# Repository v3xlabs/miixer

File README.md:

# MIIXER

An open-hardware midi controller with esp32-c3, 4 linear faders, 8 keyswitches.

> [!NOTE]
> This is a work in progress.

## Technical Specs

- **Processor**: esp32-s3
- **Inputs**
  - 4 linear potentiometers 600mm
  - 8 Cherry MX Switches
- **ICs**
  - [PCF8574T](https://jlcpcb.com/api/file/downloadByFileSystemAccessId/8624297452529963008) - I2C IO Expander
  - [ADS1115IDGS](https://jlcpcb.com/api/file/downloadByFileSystemAccessId/8624297452529963008) - I2C ADC Expander
  - [AP2127K-3.3](https://www.diodes.com/assets/Datasheets/AP2127.pdf) - 5v to 3.3v LDO
  - [USBLC6-2SC6](https://www.st.com/resource/en/datasheet/usblc6-2.pdf) - ESD Protection
- **Connectivity**:
  - USB-C (Power, Data & Flash)
  - Wifi & BLE

## Photos

See the [docs](docs) folder for the rendered schematics, PCBs, and 3D renders.

## ESPHome Compatability

Due to the fact that this devices uses common off-the-shelf I2C ICs and is esp32-c3 based, you can easily use it with ESPHome.

```yaml
# TODO: This yaml file is work in progress, its ment to give an impression, its has not been confirmed functional.
i2c:
  sda: GPIO8
  scl: GPIO9
  scan: true

# 4x Fader Input
ads1115:
  address: 0x48 # todo confirm
  update_interval: 5s
  # todo interrupt pin (io6)

# 4x Fader LEDs
tcl59208f:
  id: led_drv # optional
  address: # todo

# 8x Keyswitch Input
pcf8574:
  id: expander # optional
  address: 0x20 # todo confirm
  # todo interrupt pin (io7)

binary_sensor:
  # 8x Keyswitch Input
  - platform: pcf8574
    pin: P0
    name: "Switch 1"
    # todo add 7 more pins

sensor:
  # 4x Fader Analog Input
  - platform: ads1115
    multiplexer: 'A0_GND' # todo
    gain: 6.144 # todo
    # todo 3 more pins

output:
  # 4x Fader LEDs
  - platform: tcl59208f
    driver: led_drv # optional
    id: led1
    channel: 0
  - platform: tcl59208f
    driver: led_drv # optional
    id: led2
    channel: 1
  - platform: tcl59208f
    driver: led_drv # optional
    id: led3
    channel: 2
  - platform: tcl59208f
    driver: led_drv # optional
    id: led4
    channel: 3

light:
  # 4x Fader SK6812
  - platform: fastled_clockless
    chipset: SK6812
    pin: GPIO3
    num_leds: 4
    rgb_order: GRB
    name: "SK6812 Array"
```

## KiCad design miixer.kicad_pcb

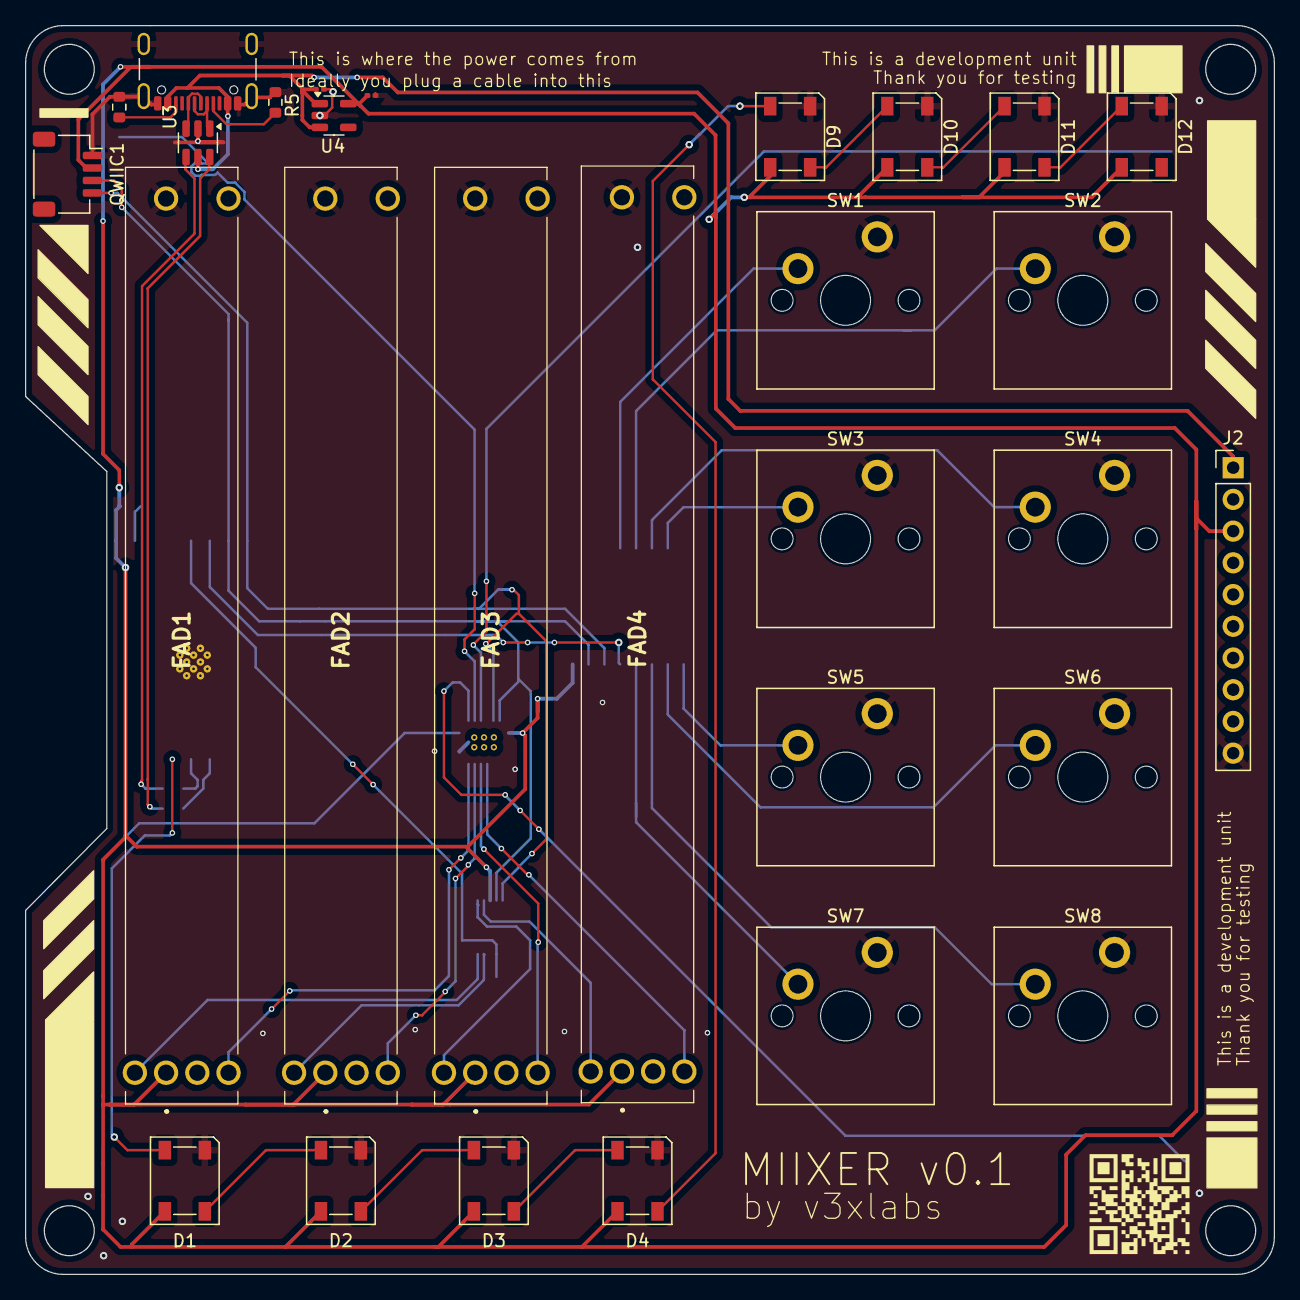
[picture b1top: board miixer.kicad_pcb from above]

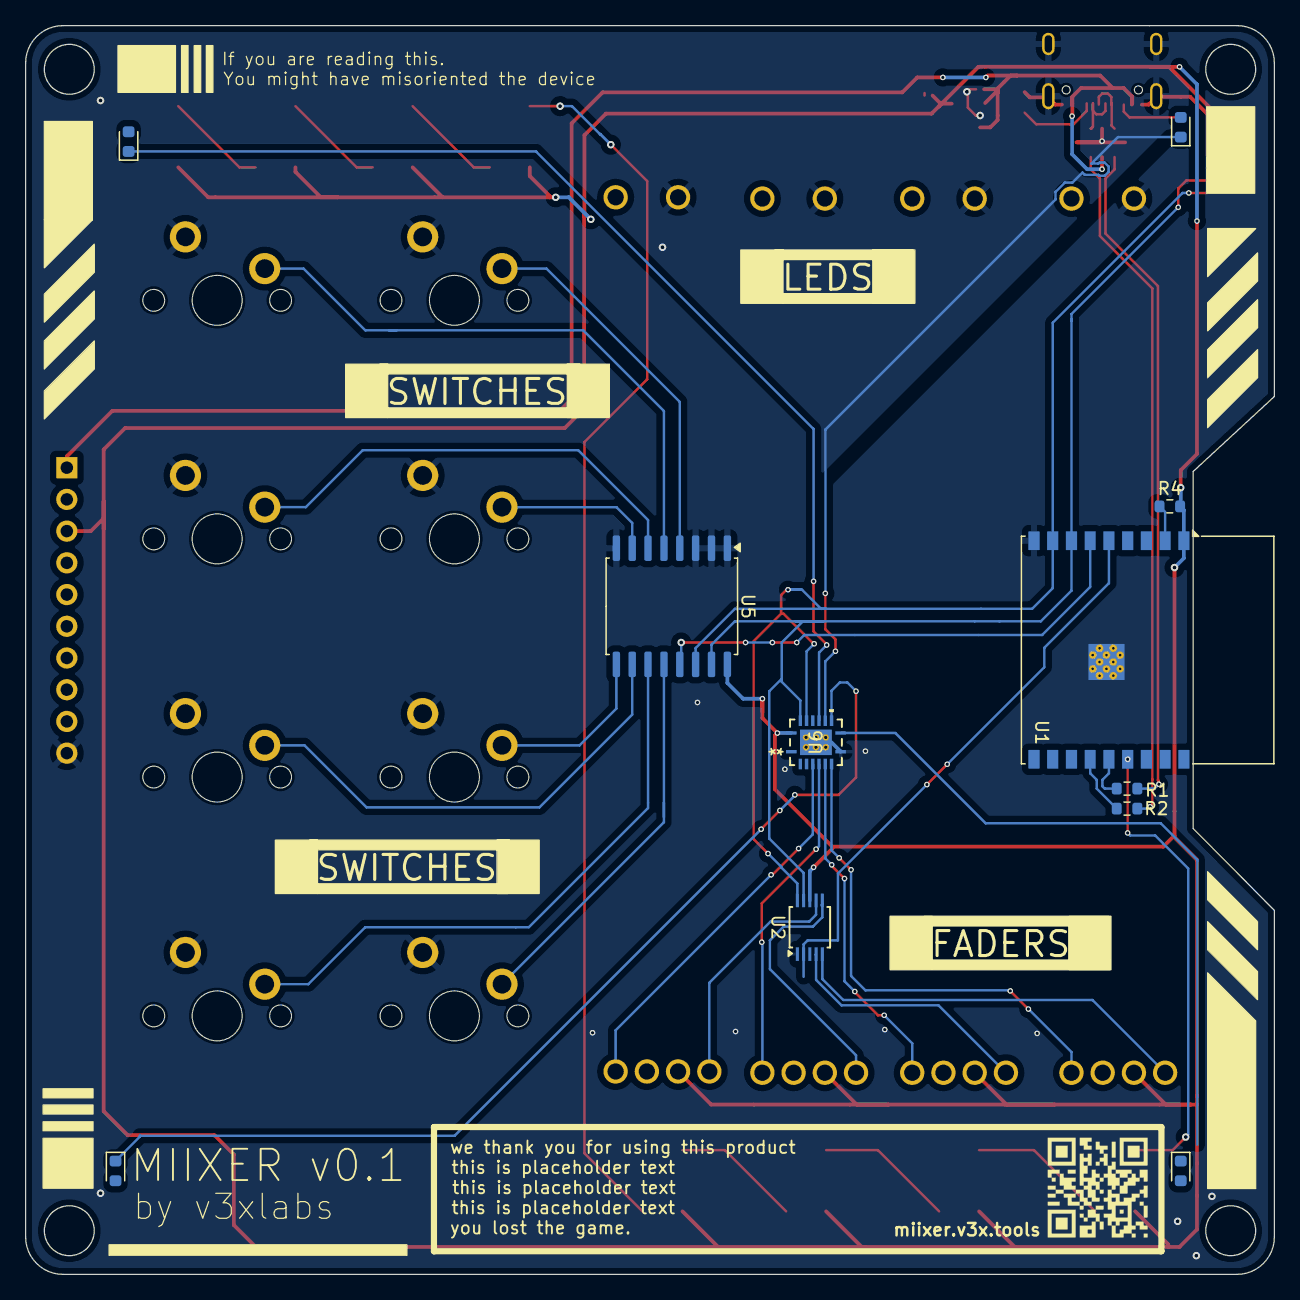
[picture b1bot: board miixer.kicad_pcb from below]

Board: 2 copper layers, 100.0 x 100.0 mm, 42 parts (12 on the bottom side), 44 nets.

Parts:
C2, C3: C; C_0201_0603Metric
D1, D2, D3, D4, D9, D10, D11, D12: SK6812; LED_SK6812_PLCC4_5.0x5.0mm_P3.2mm
D5, D6, D7, D8: LED; LED_0603_1608Metric
FAD1, FAD2, FAD3, FAD4: PTL60-15G1-103B2; PTL6015G1103B2
J1: TYPE-C 16PIN 2MD(073); USB_C_Receptacle_GCT_USB4105-xx-A_16P_TopMnt_Horizontal
J2: Conn_01x10_Pin; PinHeader_1x10_P2.54mm_Vertical
QR*****: miixer_qrcode_0.35px
QR*****#2: miixer_qrcode_0.35px
QWIIC1: Qwiic; JST_SH_SM04B-SRSS-TB_1x04-1MP_P1.00mm_Horizontal
R1, R2: 22R; R_0603_1608Metric
R4: 10k; R_0603_1608Metric
R5, R6: 5k1; R_0603_1608Metric
SW1, SW2, SW3, SW4, SW5, SW6, SW7, SW8: SW_SPST; SW_Cherry_MX_PCB_1.00u
U1: ESP32-C3-WROOM-02
U2: ADS1115IDGS; TSSOP-10_3x3mm_P0.5mm
U3: USBLC6-2SC6; SOT-23-6
U4: AP2127K-3.3; SOT-23-5
U5: PCF8574T; SOIC-16W_7.5x10.3mm_P1.27mm
U6: TLC59208FIRGYR; RGY16_2P55X2P05

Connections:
+3.3V: C3.1, D1.3 (VDD), D2.3 (VDD), D3.3 (VDD), D4.3 (VDD), D9.3 (VDD), D10.3 (VDD), D11.3 (VDD), D12.3 (VDD), FAD1.1 (CCW), FAD2.1 (CCW), FAD3.1 (CCW), FAD4.1 (CCW), J2.3, QWIIC1.2, R4.2, U1.1 (3V3), U2.8 (VDD), U4.5 (VOUT), U5.16 (VDD), U6.16 (VCC)
/Buttons/ADC_INTERRUPT: U1.5 (IO6), U2.2 (ALERT/RDY)
/Buttons/BTN_INTERRUPT: U1.6 (IO7), U5.13 (~INT)
/Buttons/EXTRA_LED_1: D5.1 (K), U6.12 (*OUT7)
/Buttons/EXTRA_LED_2: D6.1 (K), U6.10 (*OUT5)
/Buttons/EXTRA_LED_3: D7.1 (K), U6.11 (*OUT6)
/Buttons/EXTRA_LED_4: D8.1 (K), U6.9 (*OUT4)
/Buttons/FAD1_LED: FAD1.E1 (E_(-)), U6.7 (*OUT3)
/Buttons/FAD1_WIPER: FAD1.2 (WIPER), U2.5 (AIN1)
/Buttons/FAD2_LED: FAD2.E1 (E_(-)), U6.6 (*OUT2)
/Buttons/FAD2_WIPER: FAD2.2 (WIPER), U2.4 (AIN0)
/Buttons/FAD3_LED: FAD3.E1 (E_(-)), U6.5 (*OUT1)
/Buttons/FAD3_WIPER: FAD3.2 (WIPER), U2.6 (AIN2)
/Buttons/FAD4_LED: FAD4.E1 (E_(-)), U6.4 (*OUT0)
/Buttons/FAD4_WIPER: FAD4.2 (WIPER), U2.7 (AIN3)
/Buttons/LED_MCU: D1.2 (DIN), U1.15 (IO3)
/MCU/ENABLE: R4.1, U1.2 (EN)
/MCU/USBD+: R1.1, U1.14 (IO19)
/MCU/USBD-: R2.1, U1.13 (IO18)
/MCU/USB_D+: R1.2, U3.4 (I/O2)
/MCU/USB_D-: R2.2, U3.6 (I/O1)
/SCL: QWIIC1.4, U1.8 (IO9), U2.10 (SCL), U5.14 (SCL), U6.14 (SCL)
/SDA: QWIIC1.3, U1.7 (IO8), U2.9 (SDA), U5.15 (SDA), U6.15 (SDA)
/USB/CC1: J1.A5 (CC1), R5.1
/USB/CC2: J1.B5 (CC2), R6.1
/USB/USB_RAW_D+: J1.A6 (D+), J1.B6 (D+), U3.3 (I/O2)
/USB/USB_RAW_D-: J1.A7 (D-), J1.B7 (D-), U3.1 (I/O1)
GND: C2.2, C3.2, D1.1 (VSS), D2.1 (VSS), D3.1 (VSS), D4.1 (VSS), D9.1 (VSS), D10.1 (VSS), D11.1 (VSS), D12.1 (VSS), FAD1.3 (CW), FAD2.3 (CW), FAD3.3 (CW), FAD4.3 (CW), J1.A1 (GND), J1.A12 (GND), J1.B1 (GND), J1.B12 (GND), J1.S1 (SHIELD), J2.10, QWIIC1.1, R5.2, R6.2, SW1.2 (B), SW2.2 (B), SW3.2 (B), SW4.2 (B), SW5.2 (B), SW6.2 (B), SW7.2 (B), SW8.2 (B), U1.9 (GND), U1.19 (GND), U2.1 (ADDR), U2.3 (GND), U3.2 (GND), U4.2 (GND), U5.1 (A0), U5.2 (A1), U5.3 (A2), U5.8 (GND), U6.8 (GND), U6.17 (EPAD)
unnamed: D1.4 (DOUT), D2.2 (DIN)
unnamed: D2.4 (DOUT), D3.2 (DIN)
unnamed: D3.4 (DOUT), D4.2 (DIN)
unnamed: D4.4 (DOUT), D9.2 (DIN)
unnamed: D9.4 (DOUT), D10.2 (DIN)
unnamed: D10.4 (DOUT), D11.2 (DIN)
unnamed: D11.4 (DOUT), D12.2 (DIN)
unnamed: SW1.1 (A), U5.4 (P0)
unnamed: SW2.1 (A), U5.5 (P1)
unnamed: SW3.1 (A), U5.7 (P3)
unnamed: SW4.1 (A), U5.6 (P2)
unnamed: SW5.1 (A), U5.9 (P4)
unnamed: SW6.1 (A), U5.10 (P5)
unnamed: SW7.1 (A), U5.12 (P7)
unnamed: SW8.1 (A), U5.11 (P6)
VBUS: C2.1, J1.A4 (VBUS), J1.A9 (VBUS), J1.B4 (VBUS), J1.B9 (VBUS), J2.1, U3.5 (VBUS), U4.1 (VIN), U4.3 (EN)

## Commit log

2025-07-17 Introduce basic kicad project
2025-07-18 Introduce buttons and update pcb layout
2025-07-18 Make square
2025-07-18 Add keys for each fader & update layout
2025-07-18 Reorg layout and remove fader keys
2025-07-18 Update image gen
2025-07-18 Added LEDs and improved decals
2025-07-18 Update image rendering
2025-07-18 Update mcu location
2025-07-18 Update pcb
2025-07-18 Update colors
2025-07-18 Update power traces
2025-07-18 Wire buttons
2025-07-18 Introduce step file
2025-07-18 Update bom
2025-07-19 Add LED driver ic TLC59208F
2025-07-21 Add QWIIC connector
2025-07-21 Update QWIIC connector
2025-07-24 Fix layout, rewiring, and clearances
2025-07-24 Update layout & ground vias
2025-07-25 temp
2025-07-31 Update routing
